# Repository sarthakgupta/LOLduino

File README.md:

LOLduino
========

Currently Arduino IDE is used to program ATmega168, ATmega328, ATmega1280, ATmega2560, Atmega32u4. But other AVRs such as ATmega324, ATmega644, whose support is not provided by Arduino Community, can also be programmed using Arduino IDE. Tweaked the IDE a little bit so that these controllers can be programmed too. Advantages with these controllers is that they have bit more of gpio pins as required for arduino footprint so, more peripherals can be attached to these extra gpio pins. And these added peripherals can be programmed using existing Arduino libraries. 

To use the support for it you need to copy the folder LOLduino in ${arduino_directory}-> hardware, then restart the IDE. You will get a LOLduino option under Tools->Boards...
Cheers!!

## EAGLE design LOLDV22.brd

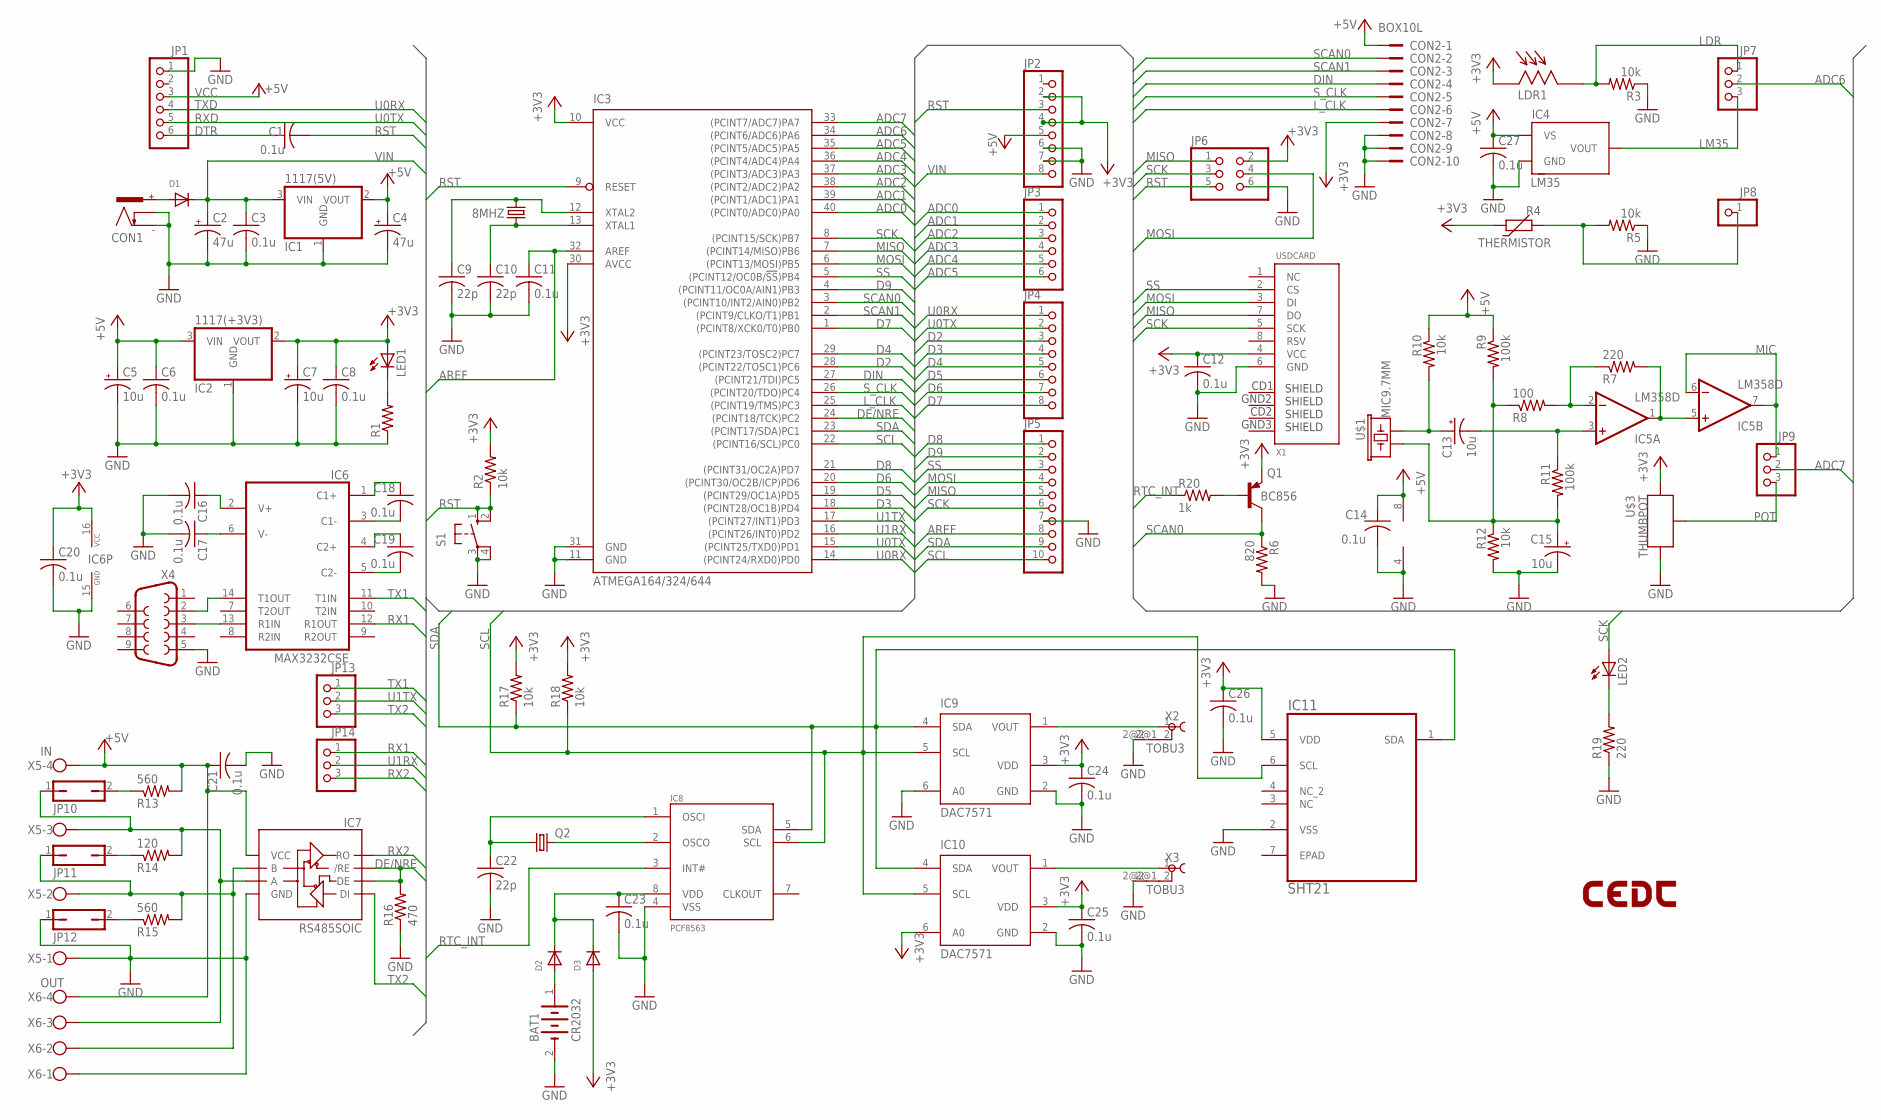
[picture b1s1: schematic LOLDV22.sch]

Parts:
8MHZ: CRYSTALHC49US; HC49US
BAT1: CR2032; BATTCON_20MM
C1, C3, C6, C8, C11, C12, C14, C16, C17, C18, C19, C20, C21, C23, C24, C25, C26, C27: 0.1u; C0805
C2, C4: 47u; E3,5-8
C5, C7, C13, C15: 10u; C/6032-28R
C9, C10, C22: 22p; C0805
CON1: POWER_CON; NEB21R
CON2: BOX10L
D1, D2, D3: DIODESMA; SMADIODE
IC1: 1117(5V); SOT223
IC2: 1117(+3V3); SOT223
IC3: ATMEGA164/324/644; DIP40
IC4: LM35; TO92
IC5: LM358D; SO08
IC6: MAX3232CSE; SO16
IC7: RS485SOIC; SO08
IC8: PCF8563; SOIC8
IC9, IC10: DAC7571; SOT23-6
IC11: SHT21; DFN300X300X110-7N
JP1, JP3: PINHD-1X6; 1X06
JP2, JP4: PINHD-1X8; 1X08
JP5: PINHD-1X10; 1X10
JP6: PINHD-2X3; 2X03
JP7, JP9, JP13, JP14: PINHD-1X3; 1X03
JP8: PINHD-1X1; 1X01
JP10, JP11, JP12: JP1Q; JP1
LDR1: CDSLDR3MM; LDR3MM
LED1, LED2: LED1206; CHIPLED_1206
LOGO1: LOGO-CEDTSILK-18MM; LOGO-CEDT-SILK-18MM
Q1: BC856; SOT23-BEC
Q2: CRYSTALTC26H; TC26H
R1: RESISTOR0805; R0805
R2, R3, R5, R10, R12, R17, R18: 10k; R0805
R4: THERMISTOR; R-5
R6: 820; R0805
R7, R19: 220; R0805
R8: 100; R0805
R9, R11: 100k; R0805
R13, R15: 560; R0805
R14: 120; R0805
R16: 470; R0805
R20: 1k; R0805
S1: 10-XX; B3F-10XX
U$1: MIC9.7MM; MIC-9.7MM
U$3: THUMBPOT
X1: USDCARD; USD-SOCKET-PUSHTYPE
X2, X3: TOBU3
X4: DB9
X5: IN; W237-4
X6: OUT; W237-4

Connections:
16MHZ: 8MHZ.2, C9.1, IC3.12 (XTAL2)
+3V3: C7.+, C8.1, C12.1, C20.1, C24.1, C25.1, C26.1, CON2.7, D3.A, IC2.2 (VOUT), IC3.10 (VCC), IC3.30 (AVCC), IC6.16 (VCC), IC9.3 (VDD), IC10.3 (VDD), IC10.6 (A0), IC11.5 (VDD), JP2.2, JP2.4, JP6.2, LDR1.P$1, LED1.A, Q1.E, R2.2, R4.1, R17.2, R18.2, U$3.1 (E), X1.4 (VCC)
+5V: C4.+, C5.+, C6.1, C14.1, C21.1, C27.1, CON2.1, IC1.2 (VOUT), IC2.3 (VIN), IC4.VS, IC5.8 (V+), IC7.8 (VCC), JP1.3, JP2.5, R9.1, R10.1, R13.2, X5.4, X6.4
ADC0: IC3.40 ((PCINT0/ADC0)PA0), JP3.1
ADC1: IC3.39 ((PCINT1/ADC1)PA1), JP3.2
ADC2: IC3.38 ((PCINT2/ADC2)PA2), JP3.3
ADC3: IC3.37 ((PCINT3/ADC3)PA3), JP3.4
ADC4: IC3.36 ((PCINT4/ADC4)PA4), JP3.5
ADC5: IC3.35 ((PCINT5/ADC5)PA5), JP3.6
ADC6: IC3.34 ((PCINT6/ADC6)PA6), JP7.2
ADC7: IC3.33 ((PCINT7/ADC7)PA7), JP9.2
AREF: C11.1, IC3.32 (AREF), JP5.8
D2: IC3.28 ((PCINT22/TOSC1)PC6), JP4.3
D3: IC3.18 ((PCINT28/OC1B)PD4), JP4.4
D4: IC3.29 ((PCINT23/TOSC2)PC7), JP4.5
D5: IC3.19 ((PCINT29/OC1A)PD5), JP4.6
D6: IC3.20 ((PCINT30/OC2B/ICP)PD6), JP4.7
D7: IC3.1 ((PCINT8/XCK0/T0)PB0), JP4.8
D8: IC3.21 ((PCINT31/OC2A)PD7), JP5.1
D9: IC3.4 ((PCINT11/OC0A/AIN1)PB3), JP5.2
DE/NRE: IC3.24 ((PCINT18/TCK)PC2), IC7.2 (/RE), IC7.3 (DE), R16.2
DIN: CON2.4, IC3.27 ((PCINT21/TDI)PC5)
DTR: C1.1, JP1.6
GND: BAT1.2 (-), C2.-, C3.2, C4.-, C5.-, C6.2, C7.-, C8.2, C9.2, C10.2, C11.2, C12.2, C14.2, C15.-, C16.2, C17.2, C20.2, C21.2, C22.2, C23.2, C24.2, C25.2, C26.2, C27.2, CON1.-, CON1.C, CON2.8, CON2.9, CON2.10, IC1.1 (GND), IC2.1 (GND), IC3.11 (GND), IC3.31 (GND), IC4.GND, IC5.4 (V-), IC6.15 (GND), IC7.5 (GND), IC8.4 (VSS), IC9.2 (GND), IC9.6 (A0), IC10.2 (GND), IC11.2 (VSS), JP1.1, JP2.6, JP2.7, JP5.7, JP6.6, JP12.1, R1.1, R3.1, R5.1, R6.2, R12.2, R16.1, R19.1, S1.3, S1.4 (P1), U$3.3 (A), X1.6 (GND), X2.2@2 (4), X3.2@2 (4), X4.5, X5.1, X6.1
LDR: JP7.1, LDR1.P$2, R3.2
LM35: IC4.VOUT, JP7.3
L_CLK: CON2.6, IC3.25 ((PCINT19/TMS)PC3)
MIC: IC5.6 (-IN), IC5.7 (OUT), JP9.1
MISO: IC3.7 ((PCINT14/MISO)PB6), JP5.5, JP6.1, X1.7 (DO)
MOSI: IC3.6 ((PCINT13/MOSI)PB5), JP5.4, JP6.4, X1.3 (DI)
unnamed: 8MHZ.1, C10.1, IC3.13 (XTAL1)
unnamed: IC5.2 (-IN), R7.1, R8.2
unnamed: C13.+, R10.2, U$1.1
unnamed: CON1.+, D1.A
unnamed: C13.-, IC5.3 (+IN), R11.1
unnamed: IC6.14 (T1OUT), X4.2
unnamed: IC5.1 (OUT), IC5.5 (+IN), R7.2
unnamed: LED1.C, R1.2
unnamed: IC10.1 (VOUT), X3.1
unnamed: IC9.1 (VOUT), X2.1
unnamed: Q1.B, R20.2
unnamed: JP8.1, R4.2, R5.2
unnamed: BAT1.1 (+), D2.A
unnamed: C19.1, IC6.4 (C2+)
unnamed: LED2.C, R19.2
unnamed: C19.2, IC6.5 (C2-)
unnamed: IC6.13 (R1IN), X4.3
unnamed: C18.2, IC6.3 (C1-)
unnamed: C18.1, IC6.1 (C1+)
unnamed: C17.1, IC6.6 (V-)
unnamed: C16.1, IC6.2 (V+)
unnamed: IC8.2 (OSCO), Q2.2
unnamed: C22.1, IC8.1 (OSCI), Q2.1
unnamed: C23.1, D2.C, D3.C, IC8.8 (VDD)
unnamed: IC7.7 (B), JP11.1, R15.2, X5.2, X6.2
unnamed: JP10.2, R13.1
unnamed: C15.+, R8.1, R9.2, R11.2, R12.1, U$1.2
unnamed: IC7.6 (A), JP10.1, R14.2, X5.3, X6.3
unnamed: JP11.2, R14.1
unnamed: JP12.2, R15.1
POT: JP9.3, U$3.2 (S)
RST: C1.2, IC3.9 (RESET), JP2.3, JP6.5, R2.1, S1.1 (S), S1.2 (S1)
RTC_INT: IC8.3 (INT#), R20.1
RX1: IC6.12 (R1OUT), JP14.1
RX2: IC7.1 (RO), JP14.3
SCAN0: CON2.2, IC3.3 ((PCINT10/INT2/AIN0)PB2), Q1.C, R6.1
SCAN1: CON2.3, IC3.2 ((PCINT9/CLKO/T1)PB1)
SCK: IC3.8 ((PCINT15/SCK)PB7), JP5.6, JP6.3, LED2.A, X1.5 (SCK)
SCL: IC3.22 ((PCINT16/SCL)PC0), IC8.6 (SCL), IC9.5 (SCL), IC10.5 (SCL), IC11.6 (SCL), JP5.10, R18.1
SDA: IC3.23 ((PCINT17/SDA)PC1), IC8.5 (SDA), IC9.4 (SDA), IC10.4 (SDA), IC11.1 (SDA), JP5.9, R17.1
SS: IC3.5 ((PCINT12/OC0B/!SS!)PB4), JP5.3, X1.2 (CS)
S_CLK: CON2.5, IC3.26 ((PCINT20/TDO)PC4)
TX1: IC6.11 (T1IN), JP13.1
TX2: IC7.4 (DI), JP13.3
U0RX: IC3.14 ((PCINT24/RXD0)PD0), JP1.4, JP4.1
U0TX: IC3.15 ((PCINT25/TXD0)PD1), JP1.5, JP4.2
U1RX: IC3.16 ((PCINT26/INT0)PD2), JP14.2
U1TX: IC3.17 ((PCINT27/INT1)PD3), JP13.2
VIN: C2.+, C3.1, D1.C, IC1.3 (VIN), JP2.8

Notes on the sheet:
TXD RXD
VCC

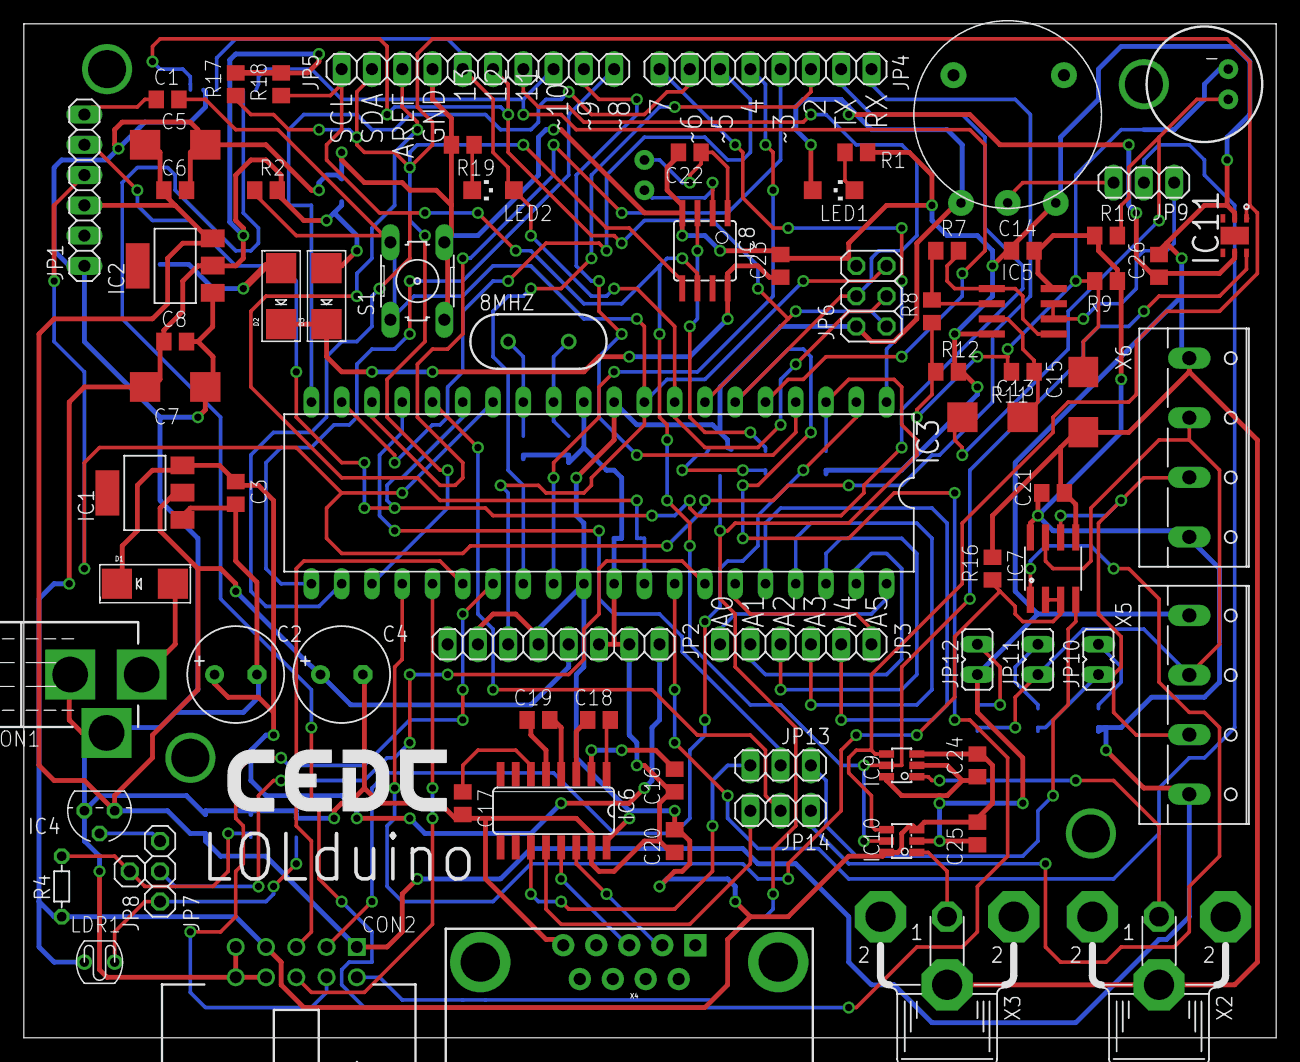
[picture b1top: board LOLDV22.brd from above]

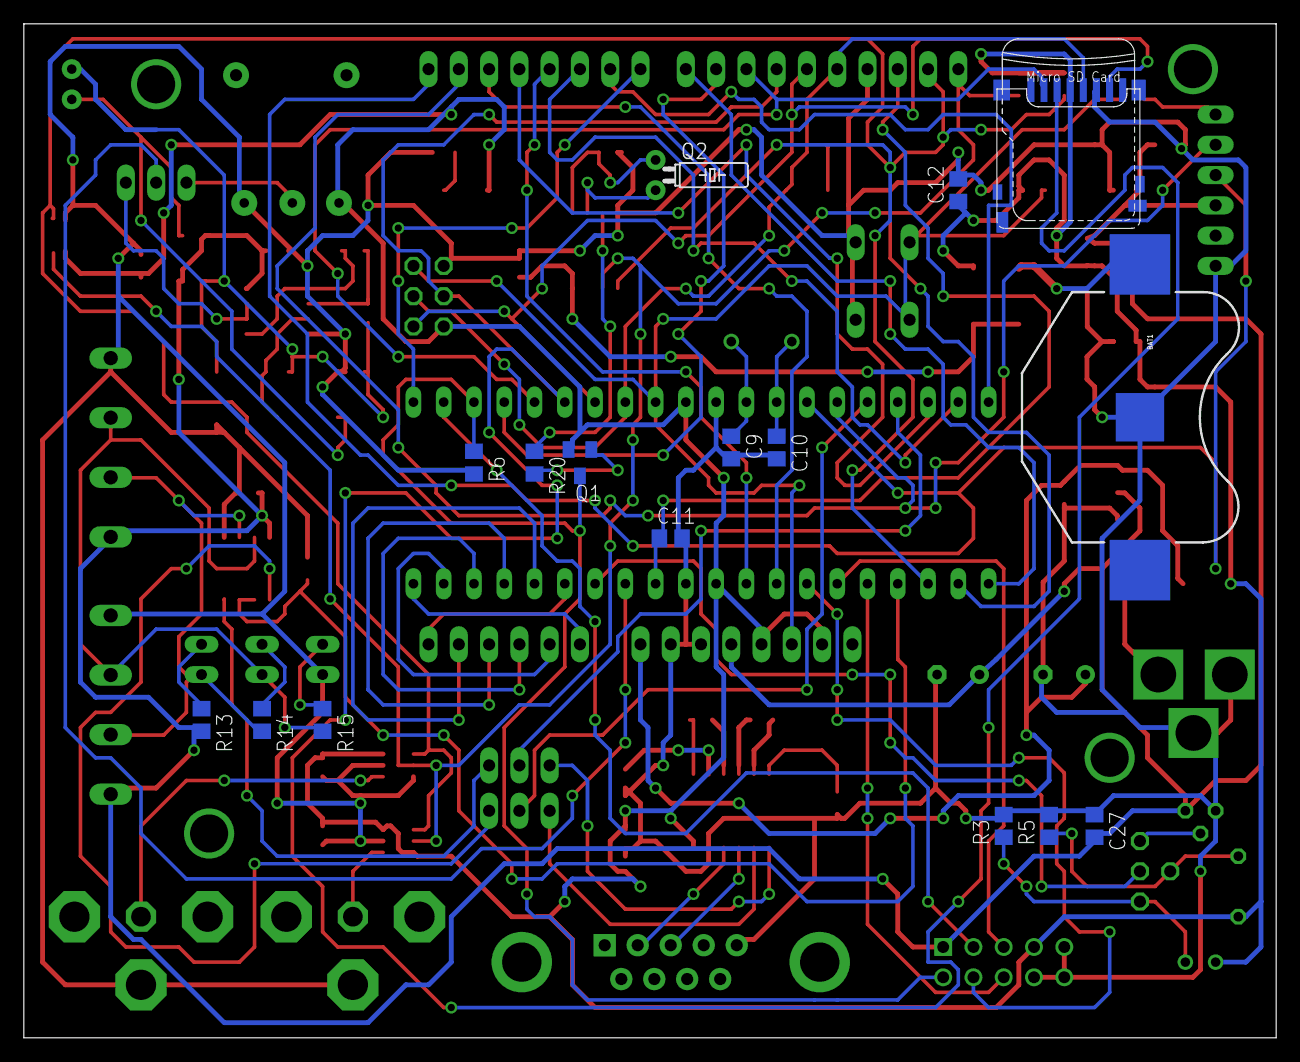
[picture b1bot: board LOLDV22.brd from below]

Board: 2 copper layers, 105.1 x 85.1 mm, 94 parts (16 on the bottom side), 79 nets.

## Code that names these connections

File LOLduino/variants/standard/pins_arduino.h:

/*
  pins_arduino.h - Pin definition functions for Arduino
  Part of Arduino - http://www.arduino.cc/

  Copyright (c) 2007 David A. Mellis

  This library is free software; you can redistribute it and/or
  modify it under the terms of the GNU Lesser General Public
  License as published by the Free Software Foundation; either
  version 2.1 of the License, or (at your option) any later version.

  This library is distributed in the hope that it will be useful,
  but WITHOUT ANY WARRANTY; without even the implied warranty of
  MERCHANTABILITY or FITNESS FOR A PARTICULAR PURPOSE.  See the GNU
  Lesser General Public License for more details.

  You should have received a copy of the GNU Lesser General
  Public License along with this library; if not, write to the
  Free Software Foundation, Inc., 59 Temple Place, Suite 330,
  Boston, MA  02111-1307  USA

  $Id: wiring.h 249 2007-02-03 16:52:51Z mellis $

  Changelog
  -----------
  11/25/11  - ryan@ryanmsutton.com - Add pins for Sanguino 644P and 1284P
  07/15/12  - ryan@ryanmsutton.com - Updated for arduino0101
*/

#ifndef Pins_Arduino_h
#define Pins_Arduino_h

#include <avr/pgmspace.h>

#define NOT_A_PIN 0
#define NOT_A_PORT 0

#define NOT_ON_TIMER 0
#define TIMER0A 1
#define TIMER0B 2
#define TIMER1A 3
#define TIMER1B 4
#define TIMER2  5
#define TIMER2A 6
#define TIMER2B 7

#define TIMER3A 8
#define TIMER3B 9
#define TIMER3C 10
#define TIMER4A 11
#define TIMER4B 12
#define TIMER4C 13
#define TIMER5A 14
#define TIMER5B 15
#define TIMER5C 16

const static uint8_t SS   = 10;
const static uint8_t MOSI = 11;
const static uint8_t MISO = 12;
const static uint8_t SCK  = 13;

static const uint8_t SDA = 18;
static const uint8_t SCL = 19;
static const uint8_t LED_BUILTIN = 13;

static const uint8_t A0 = 31;
static const uint8_t A1 = 30;
static const uint8_t A2 = 29;
static const uint8_t A3 = 28;
static const uint8_t A4 = 27;
static const uint8_t A5 = 26;
static const uint8_t A6 = 25;
static const uint8_t A7 = 24;

// On the ATmega1280, the addresses of some of the port registers are
// greater than 255, so we can't store them in uint8_t's.
// extern const uint16_t PROGMEM port_to_mode_PGM[];
// extern const uint16_t PROGMEM port_to_input_PGM[];
// extern const uint16_t PROGMEM port_to_output_PGM[];

// extern const uint8_t PROGMEM digital_pin_to_port_PGM[];
// extern const uint8_t PROGMEM digital_pin_to_bit_PGM[];
// extern const uint8_t PROGMEM digital_pin_to_bit_mask_PGM[];
// extern const uint8_t PROGMEM digital_pin_to_timer_PGM[];

// ATMEL ATMEGA644P / SANGUINO
//
//                   +---\/---+
//  INT0 (D 0) PB0  1|        |40  PA0 (AI 0 / D31)
//  INT1 (D 1) PB1  2|        |39  PA1 (AI 1 / D30)
//  INT2 (D 2) PB2  3|        |38  PA2 (AI 2 / D29)
//   PWM (D 3) PB3  4|        |37  PA3 (AI 3 / D28)
//   PWM (D 4) PB4  5|        |36  PA4 (AI 4 / D27)
//  MOSI (D 5) PB5  6|        |35  PA5 (AI 5 / D26)
//  MISO (D 6) PB6  7|        |34  PA6 (AI 6 / D25)
//   SCK (D 7) PB7  8|        |33  PA7 (AI 7 / D24)
//             RST  9|        |32  AREF
//             VCC 10|        |31  GND 
//             GND 11|        |30  AVCC
//           XTAL2 12|        |29  PC7 (D 23)
//           XTAL1 13|        |28  PC6 (D 22)
//  RX0 (D 8)  PD0 14|        |27  PC5 (D 21) TDI
//  TX0 (D 9)  PD1 15|        |26  PC4 (D 20) TDO
//  RX1 (D 10) PD2 16|        |25  PC3 (D 19) TMS
//  TX1 (D 11) PD3 17|        |24  PC2 (D 18) TCK
//  PWM (D 12) PD4 18|        |23  PC1 (D 17) SDA
//  PWM (D 13) PD5 19|        |22  PC0 (D 16) SCL
//  PWM (D 14) PD6 20|        |21  PD7 (D 15) PWM
//                   +--------+
//
#define NUM_DIGITAL_PINS            24
#define NUM_ANALOG_INPUTS           8
#define analogInputToDigitalPin(p)  ((p < 7) ? (p) + 24 : -1)

//#define digitalPinHasPWM(p)         ((p) == 3 || (p) == 4 || (p) == 12 || (p) == 13 || (p) == 14 || (p) == 15 )
#define digitalPinHasPWM(p)         ((p) == 3 || (p) == 5 || (p) == 6 || (p) == 8 || (p) == 9 || (p) == 10 )

#define PA 1
#define PB 2
#define PC 3
#define PD 4
#define PE 5
#define PF 6
#define PG 7
#define PH 8
#define PJ 10
#define PK 11
#define PL 12

#ifdef ARDUINO_MAIN
// these arrays map port names (e.g. port B) to the
// appropriate addresses for various functions (e.g. reading
// and writing)
const uint16_t PROGMEM port_to_mode_PGM[] =
{
        NOT_A_PORT,
        (uint16_t) &DDRA,
        (uint16_t) &DDRB,
        (uint16_t) &DDRC,
        (uint16_t) &DDRD,
};

const uint16_t PROGMEM port_to_output_PGM[] =
{
        NOT_A_PORT,
        (uint16_t) &PORTA,
        (uint16_t) &PORTB,
        (uint16_t) &PORTC,
        (uint16_t) &PORTD,
};
const uint16_t PROGMEM port_to_input_PGM[] =
{
        NOT_A_PORT,
        (uint16_t) &PINA,
        (uint16_t) &PINB,
        (uint16_t) &PINC,
        (uint16_t) &PIND,
};
const uint8_t PROGMEM digital_pin_to_port_PGM[] =
{
        PD, /* 0 */
        PD,
        PC,
        PD,
        PC,
        PD,
        PD,
        PB,
        PD, /* 8 */
        PB,
        PB,
        PB,
        PB,
        PB,
        PB,
        PB,
        PD, /* 16 */
        PD,
        PC,
        PC,
        PC,
        PC,
        PC,
        PC,
        PA, /* 24 */
        PA,
        PA,
        PA,
        PA,
        PA,
        PA,
        PA  /* 31 */
};
const uint8_t PROGMEM digital_pin_to_bit_mask_PGM[] =
{
        _BV(0), /* 0, port D */
        _BV(1),
        _BV(6), /* 2, port C */
        _BV(4), /* 3, port D */
        _BV(7), /* 4, port C */
        _BV(5),
        _BV(6),
        _BV(0), /* 7, port B */
        _BV(7), /* 8, port D */
        _BV(3), /* 9, port B */
        _BV(4),
        _BV(5),
        _BV(6),
        _BV(7),
        _BV(1),
        _BV(2),
        _BV(2), /* 16, port D */
        _BV(3),
        _BV(1), /* 18, port C */
        _BV(0),
        _BV(2),
        _BV(3),
        _BV(4),
        _BV(5),
        _BV(7), /* 24, port A */
        _BV(6),
        _BV(5),
        _BV(4),
        _BV(3),
        _BV(2),
        _BV(1),
        _BV(0)
};
const uint8_t PROGMEM digital_pin_to_timer_PGM[] =
{
        NOT_ON_TIMER,   /* 8  - PD0 */
        NOT_ON_TIMER,   /* 9  - PD1 */
        NOT_ON_TIMER,   /* 22 - PC6 */
        TIMER1B,        /* 12 - PD4 */
        NOT_ON_TIMER,   /* 23 - PC7 */
        TIMER1A,        /* 13 - PD5 */
        TIMER2B,        /* 14 - PD6 */
        NOT_ON_TIMER,   /* 0  - PB0 */

        TIMER2A,        /* 15 - PD7 */
        TIMER0A,        /* 3  - PB3 */
        TIMER0B,        /* 4  - PB4 */
        NOT_ON_TIMER,   /* 5  - PB5 */
        NOT_ON_TIMER,   /* 6  - PB6 */
        NOT_ON_TIMER,   /* 7  - PB7 */
        NOT_ON_TIMER,   /* 1  - PB1 */
        NOT_ON_TIMER,   /* 2  - PB2 */

        NOT_ON_TIMER,   /* 10 - PD2 */
        NOT_ON_TIMER,   /* 11 - PD3 */
        NOT_ON_TIMER,   /* 17 - PC1 */
        NOT_ON_TIMER,   /* 16 - PC0 */
        NOT_ON_TIMER,   /* 18 - PC2 */
        NOT_ON_TIMER,   /* 19 - PC3 */
        NOT_ON_TIMER,   /* 20 - PC4 */
        NOT_ON_TIMER,   /* 21 - PC5 */

        NOT_ON_TIMER,   /* 24 - PA0 */
        NOT_ON_TIMER,   /* 25 - PA1 */
        NOT_ON_TIMER,   /* 26 - PA2 */
        NOT_ON_TIMER,   /* 27 - PA3 */
        NOT_ON_TIMER,   /* 28 - PA4 */
        NOT_ON_TIMER,   /* 29 - PA5 */
        NOT_ON_TIMER,   /* 30 - PA6 */
        NOT_ON_TIMER   /* 31 - PA7 */
};
#endif
#endif

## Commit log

2013-11-22 LOLduino
2013-11-22 schematic and layout
2013-11-22 Readme
2013-12-09 schematic and readme
2013-12-09 read me
2013-12-19 schematic update

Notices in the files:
parts and their libraries:
sparkfun: Licensing: CC v3.0 Share-Alike You are welcome to use this library for commercial purposes.
